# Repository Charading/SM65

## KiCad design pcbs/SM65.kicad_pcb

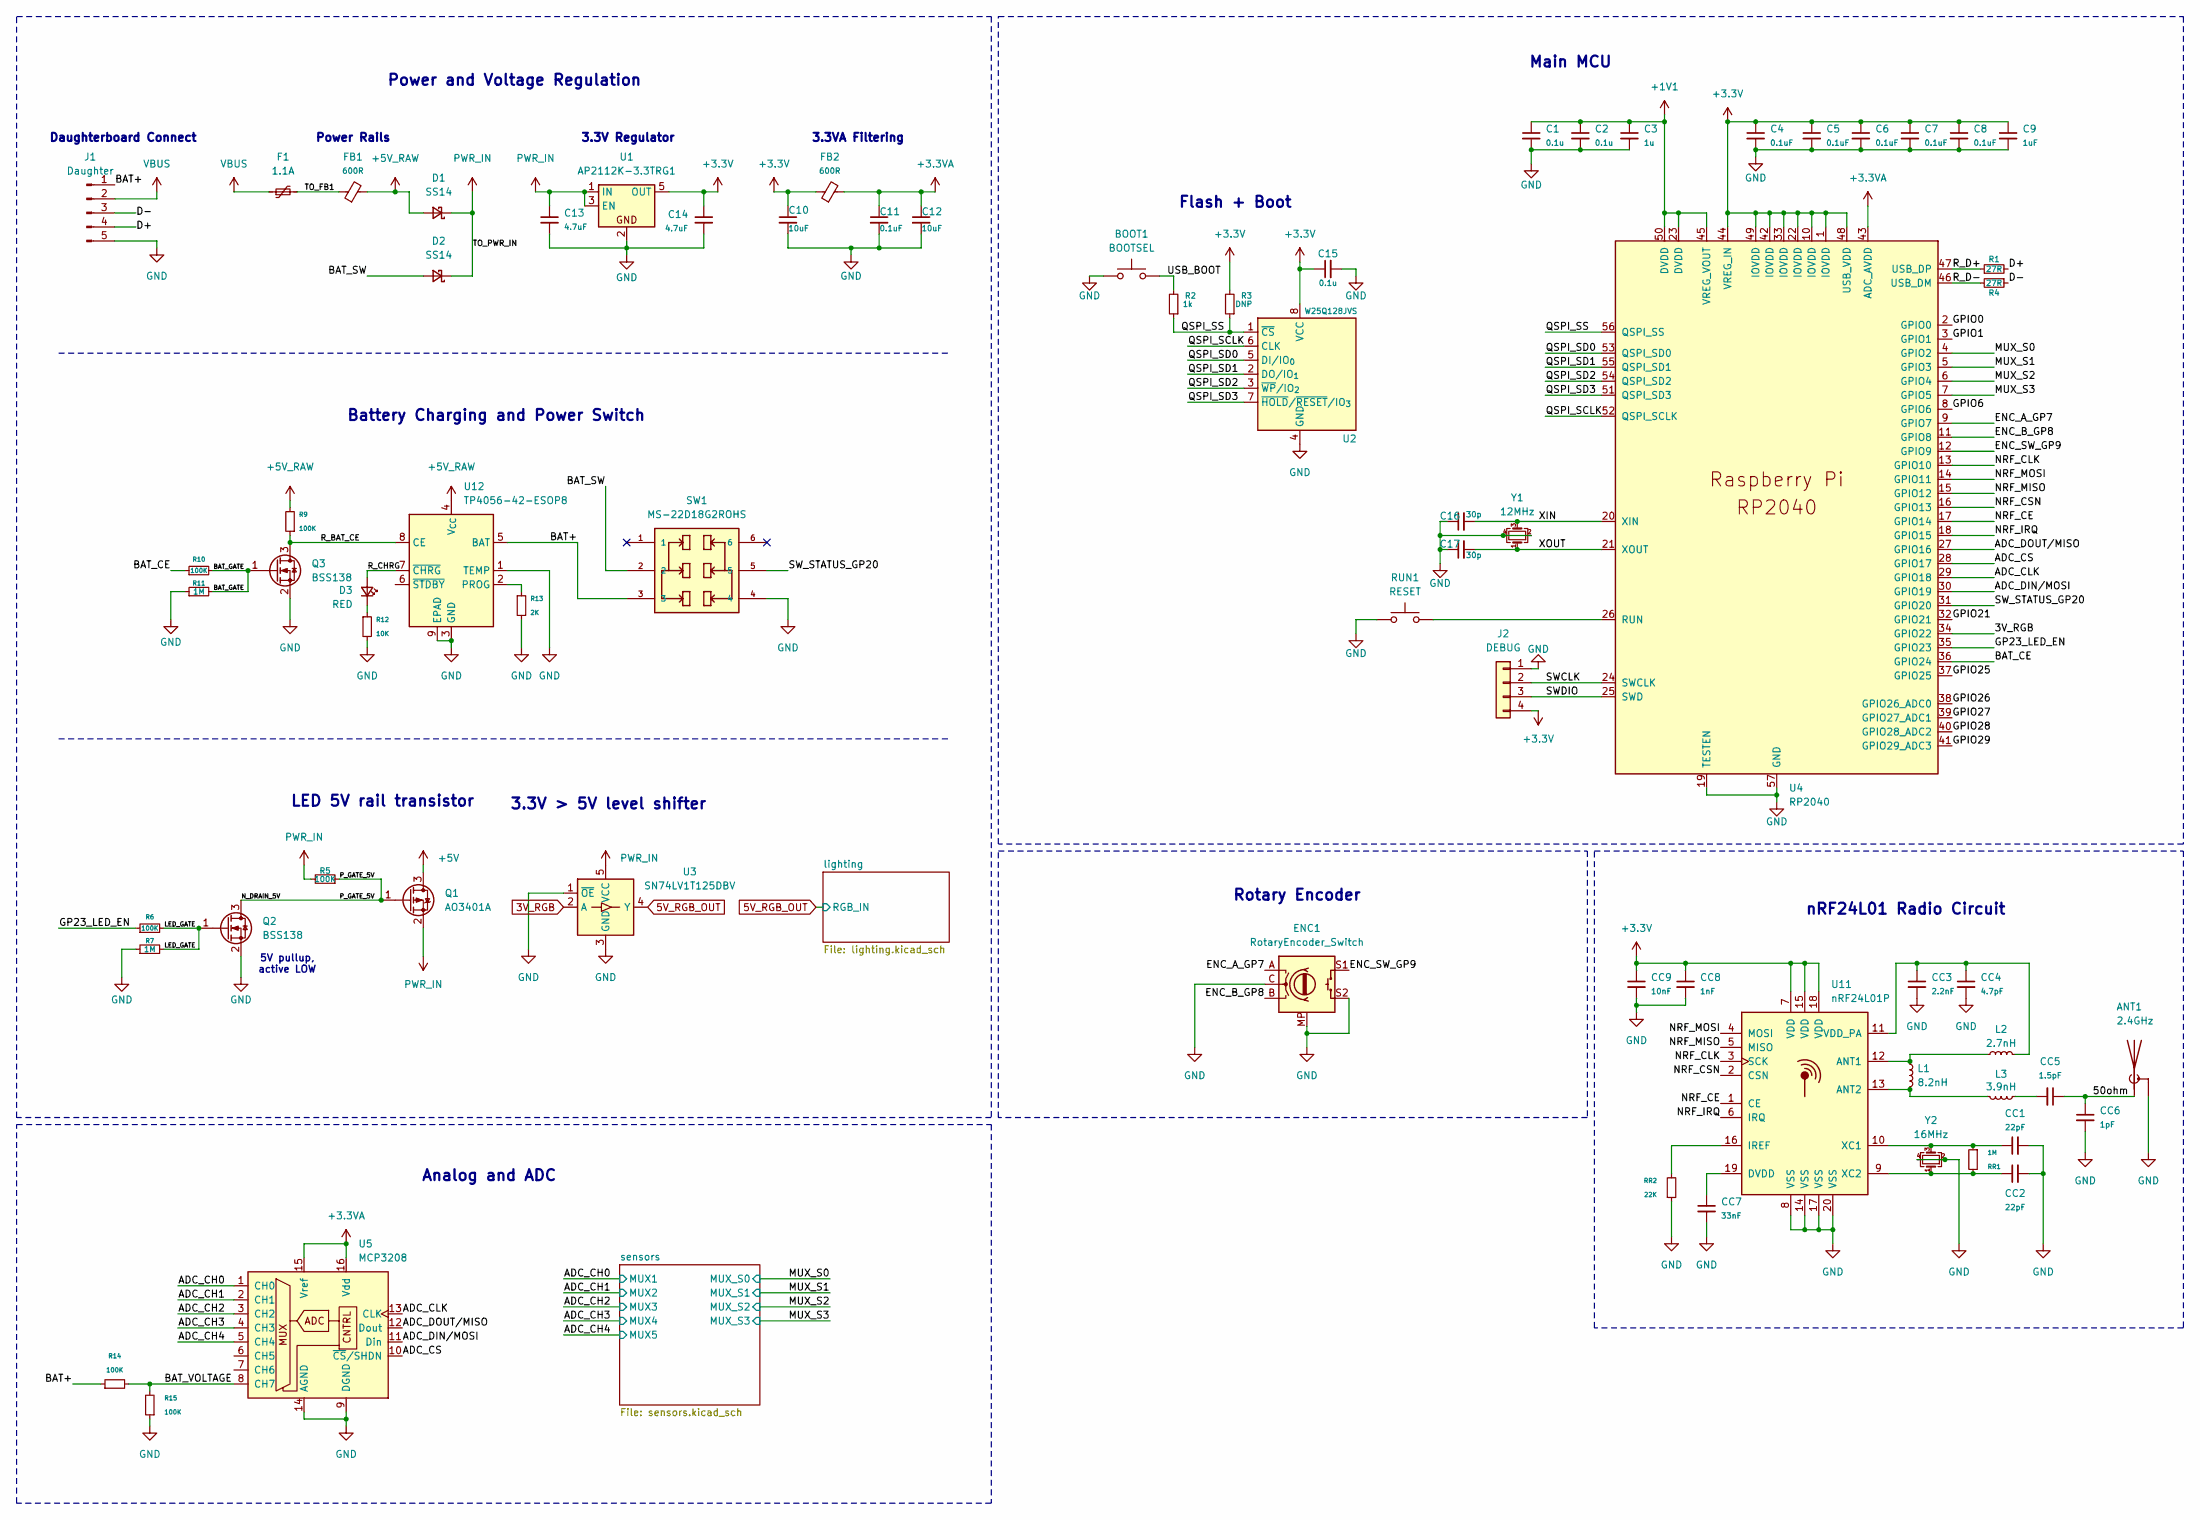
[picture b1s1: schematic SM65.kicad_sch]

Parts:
ANT1: 2.4GHz; MIFA_2.4GHz_Antenna
BOOT1: BOOTSEL; SW_SPST_EVQP2_MiddlePushTravel_H2.5mm
C1, C2: 0.1u; C_0402
C3: 1u; C_0402
C4, C5, C6, C7, C8: 0.1uF; C_0402
C9: 1uF; C_0402
C10, C12: 10uF; C_0603
C11: 0.1uF; C_0603
C13, C14: 4.7uF; C_0603
C15: 0.1u; C_0603
C16, C17: 30p; C_0402
CC1, CC2: 22pF; C_0402
CC3: 2.2nF; C_0402
CC4: 4.7pF; C_0402
CC5: 1.5pF; C_0402
CC6: 1pF; C_0402
CC7: 33nF; C_0402
CC8: 1nF; C_0402
CC9: 10nF; C_0402
D1, D2: SS14; D_SMA
D3: RED; LED_0402_1005Metric
ENC1: RotaryEncoder_Switch; RotaryEncoder_MX_EC11_CircularMountingHoles
F1: 1.1A; Fuse_0603_1608Metric
FB1, FB2: 600R; Ferrite_0603_1608Metric
J1: Daughter; JST_GH_BM05B-GHS-TBT_1x05-1MP_P1.25mm_Vertical
J2: DEBUG; PinHeader_1x04_P1.27mm_Vertical; Part Number 1-0401FBV0T
L1: 8.2nH; R_0402
L2: 2.7nH; R_0402
L3: 3.9nH; R_0402
Q1: AO3401A; SOT-23
Q2, Q3: BSS138; SOT-23
R1, R4: 27R; R_0603_1608Metric_Pad0.98x0.95mm_HandSolder
R2: 1k; R_0603
R3: DNP; R_0603
R5, R6, R9, R10, R14, R15: 100K; R_0603
R7, R11: 1M; R_0603
R12: 10K; R_0402
R13: 2K; R_0603
RR1: 1M; R_0402
RR2: 22K; R_0402
RUN1: RESET; SW_SPST_EVQP2_MiddlePushTravel_H2.5mm
SW1: MS-22D18G2ROHS; MS-22D18_SMD
U1: AP2112K-3.3TRG1; SOT-23-5
U2: W25Q128JVS; SOIC-8_5.3x5.3mm_P1.27mm
U3: SN74LV1T125DBV; SOT-23-5
U4: RP2040; QFN-56-1EP_7x7mm_P0.4mm_EP3.2x3.2mm
U5: MCP3208; SOIC-16_3.9x9.9mm_P1.27mm
U11: nRF24L01P; QFN-20-1EP_4x4mm_P0.5mm_EP2.5x2.5mm
U12: TP4056-42-ESOP8; SOIC-8-1EP_3.9x4.9mm_P1.27mm_EP2.41x3.3mm
Y1: 12MHz; Crystal_SMD_3225-4Pin_3.2x2.5mm
Y2: 16MHz; Crystal_SMD_3225-4Pin_3.2x2.5mm

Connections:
3V_RGB: U3.2 (A), U4.34 (GPIO22)
5V_RGB_OUT: U3.4 (Y); also elsewhere on the board
+1V1: C1.1, C2.1, C3.1, U4.23 (DVDD), U4.45 (VREG_VOUT), U4.50 (DVDD)
+3.3V: C4.1, C5.1, C6.1, C7.1, C8.1, C9.1, C10.1, C14.1, C15.1, CC8.1, CC9.1, FB2.1, J2.4, R3.2, U1.5 (OUT), U2.8 (VCC), U4.1 (IOVDD), U4.10 (IOVDD), U4.22 (IOVDD), U4.33 (IOVDD), U4.42 (IOVDD), U4.44 (VREG_IN), U4.48 (USB_VDD), U4.49 (IOVDD), U11.7 (VDD), U11.15 (VDD), U11.18 (VDD); also elsewhere on the board
+3.3VA: C11.1, C12.1, FB2.2, U4.43 (ADC_AVDD), U5.15 (Vref), U5.16 (Vdd)
+5V: Q1.3 (D); also elsewhere on the board
+5V_RAW: D1.2 (A), FB1.2, R9.2, U12.4 (V_{CC})
/50ohm: ANT1.1 (A), CC5.1, CC6.1
/ADC_CH0: U5.1 (CH0); also elsewhere on the board
/ADC_CH1: U5.2 (CH1); also elsewhere on the board
/ADC_CH2: U5.3 (CH2); also elsewhere on the board
/ADC_CH3: U5.4 (CH3); also elsewhere on the board
/ADC_CH4: U5.5 (CH4); also elsewhere on the board
/ADC_CLK: U4.29 (GPIO18), U5.13 (CLK)
/ADC_CS: U4.28 (GPIO17), U5.10 (~CS/SHDN)
/ADC_DIN/MOSI: U4.30 (GPIO19), U5.11 (Din)
/ADC_DOUT/MISO: U4.27 (GPIO16), U5.12 (Dout)
/BAT+: J1.1, R14.1, SW1.3, U12.5 (BAT)
/BAT_CE: R10.1, U4.36 (GPIO24)
/BAT_GATE: Q3.1 (G), R10.2, R11.2
/BAT_SW: D2.2 (A), SW1.2
/BAT_VOLTAGE: R14.2, R15.2, U5.8 (CH7)
/D+: J1.4, R1.2
/D-: J1.3, R4.1
/ENC_A_GP7: ENC1.A, U4.9 (GPIO7)
/ENC_B_GP8: ENC1.B, U4.11 (GPIO8)
/ENC_SW_GP9: ENC1.S1, U4.12 (GPIO9)
/GP23_LED_EN: R6.1, U4.35 (GPIO23)
/GPIO0: U4.2 (GPIO0)
/GPIO1: U4.3 (GPIO1)
/GPIO6: U4.8 (GPIO6)
/GPIO21: U4.32 (GPIO21)
/GPIO25: U4.37 (GPIO25)
/GPIO26: U4.38 (GPIO26_ADC0)
/GPIO27: U4.39 (GPIO27_ADC1)
/GPIO28: U4.40 (GPIO28_ADC2)
/GPIO29: U4.41 (GPIO29_ADC3)
/LED_GATE: Q2.1 (G), R6.2, R7.2
/MUX_S0: U4.4 (GPIO2); also elsewhere on the board
/MUX_S1: U4.5 (GPIO3); also elsewhere on the board
/MUX_S2: U4.6 (GPIO4); also elsewhere on the board
/MUX_S3: U4.7 (GPIO5); also elsewhere on the board
/NRF_CE: U4.17 (GPIO14), U11.1 (CE)
/NRF_CLK: U4.13 (GPIO10), U11.3 (SCK)
/NRF_CSN: U4.16 (GPIO13), U11.2 (CSN)
/NRF_IRQ: U4.18 (GPIO15), U11.6 (IRQ)
/NRF_MISO: U4.15 (GPIO12), U11.5 (MISO)
/NRF_MOSI: U4.14 (GPIO11), U11.4 (MOSI)
/N_DRAIN_5V: Q1.1 (G), Q2.3 (D), R5.1
/QSPI_SCLK: U2.6 (CLK), U4.52 (QSPI_SCLK)
/QSPI_SD0: U2.5 (DI/IO_{0}), U4.53 (QSPI_SD0)
/QSPI_SD1: U2.2 (DO/IO_{1}), U4.55 (QSPI_SD1)
/QSPI_SD2: U2.3 (~WP/IO_{2}), U4.54 (QSPI_SD2)
/QSPI_SD3: U2.7 (~HOLD/~RESET/IO_{3}), U4.51 (QSPI_SD3)
/QSPI_SS: R2.1, R3.1, U2.1 (~CS), U4.56 (QSPI_SS)
/R_BAT_CE: Q3.3 (D), R9.1, U12.8 (CE)
/R_CHRG: D3.2 (A), U12.7 (~CHRG)
/R_D+: R1.1, U4.47 (USB_DP)
/R_D-: R4.2, U4.46 (USB_DM)
/SWCLK: J2.2, U4.24 (SWCLK)
/SWDIO: J2.3, U4.25 (SWD)
/SW_STATUS_GP20: SW1.5, U4.31 (GPIO20)
/TO_FB1: F1.2, FB1.1
/USB_BOOT: BOOT1.2, R2.2
/XIN: C16.2, U4.20 (XIN), Y1.3
/XOUT: C17.2, U4.21 (XOUT), Y1.1
GND: ANT1.2 (Shield), BOOT1.1, C1.2, C2.2, C3.2, C4.2, C5.2, C6.2, C7.2, C8.2, C9.2, C10.2, C11.2, C12.2, C13.2, C14.2, C15.2, C16.1, C17.1, CC1.2, CC2.2, CC3.2, CC4.2, CC6.2, CC7.2, CC8.2, CC9.2, ENC1.C, ENC1.MP, ENC1.S2, J1.5, J2.1, Q2.2 (S), Q3.2 (S), R7.1, R11.1, R12.2, R13.2, R15.1, RR2.1, RUN1.1, SW1.4, U1.2, U2.4 (GND), U3.1 (~OE), U3.3 (GND), U4.19 (TESTEN), U4.57 (GND), U5.9 (DGND), U5.14 (AGND), U11.8 (VSS), U11.14 (VSS), U11.17 (VSS), U11.20 (VSS), U12.1 (TEMP), U12.3 (GND), U12.9 (EPAD), Y1.2, Y1.4, Y2.2, Y2.4; also elsewhere on the board
unnamed: CC5.2, L3.1
unnamed: D3.1 (K), R12.1
unnamed: RUN1.2, U4.26 (RUN)
unnamed: L1.1, L2.1, U11.12 (ANT1)
unnamed: L1.2, L3.2, U11.13 (ANT2)
unnamed: CC7.1, U11.19 (DVDD)
unnamed: RR2.2, U11.16 (IREF)
unnamed: CC3.1, CC4.1, L2.2, U11.11 (VDD_PA)
unnamed: CC1.1, RR1.1, U11.10 (XC1), Y2.3
unnamed: CC2.1, RR1.2, U11.9 (XC2), Y2.1
unnamed: R13.1, U12.2 (PROG)
PWR_IN: C13.1, D1.1 (K), D2.1 (K), Q1.2 (S), R5.2, U1.1 (IN), U1.3 (EN), U3.5 (VCC)
VBUS: F1.1, J1.2

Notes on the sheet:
LED 5V rail transistor
3.3V > 5V level shifter
Rotary Encoder
Flash + Boot
5V pullup, active LOW
Battery Charging and Power Switch
Daughterboard Connect
Analog and ADC
3.3V Regulator
nRF24L01 Radio Circuit
Power and Voltage Regulation
3.3VA Filtering
Main MCU
Power Rails

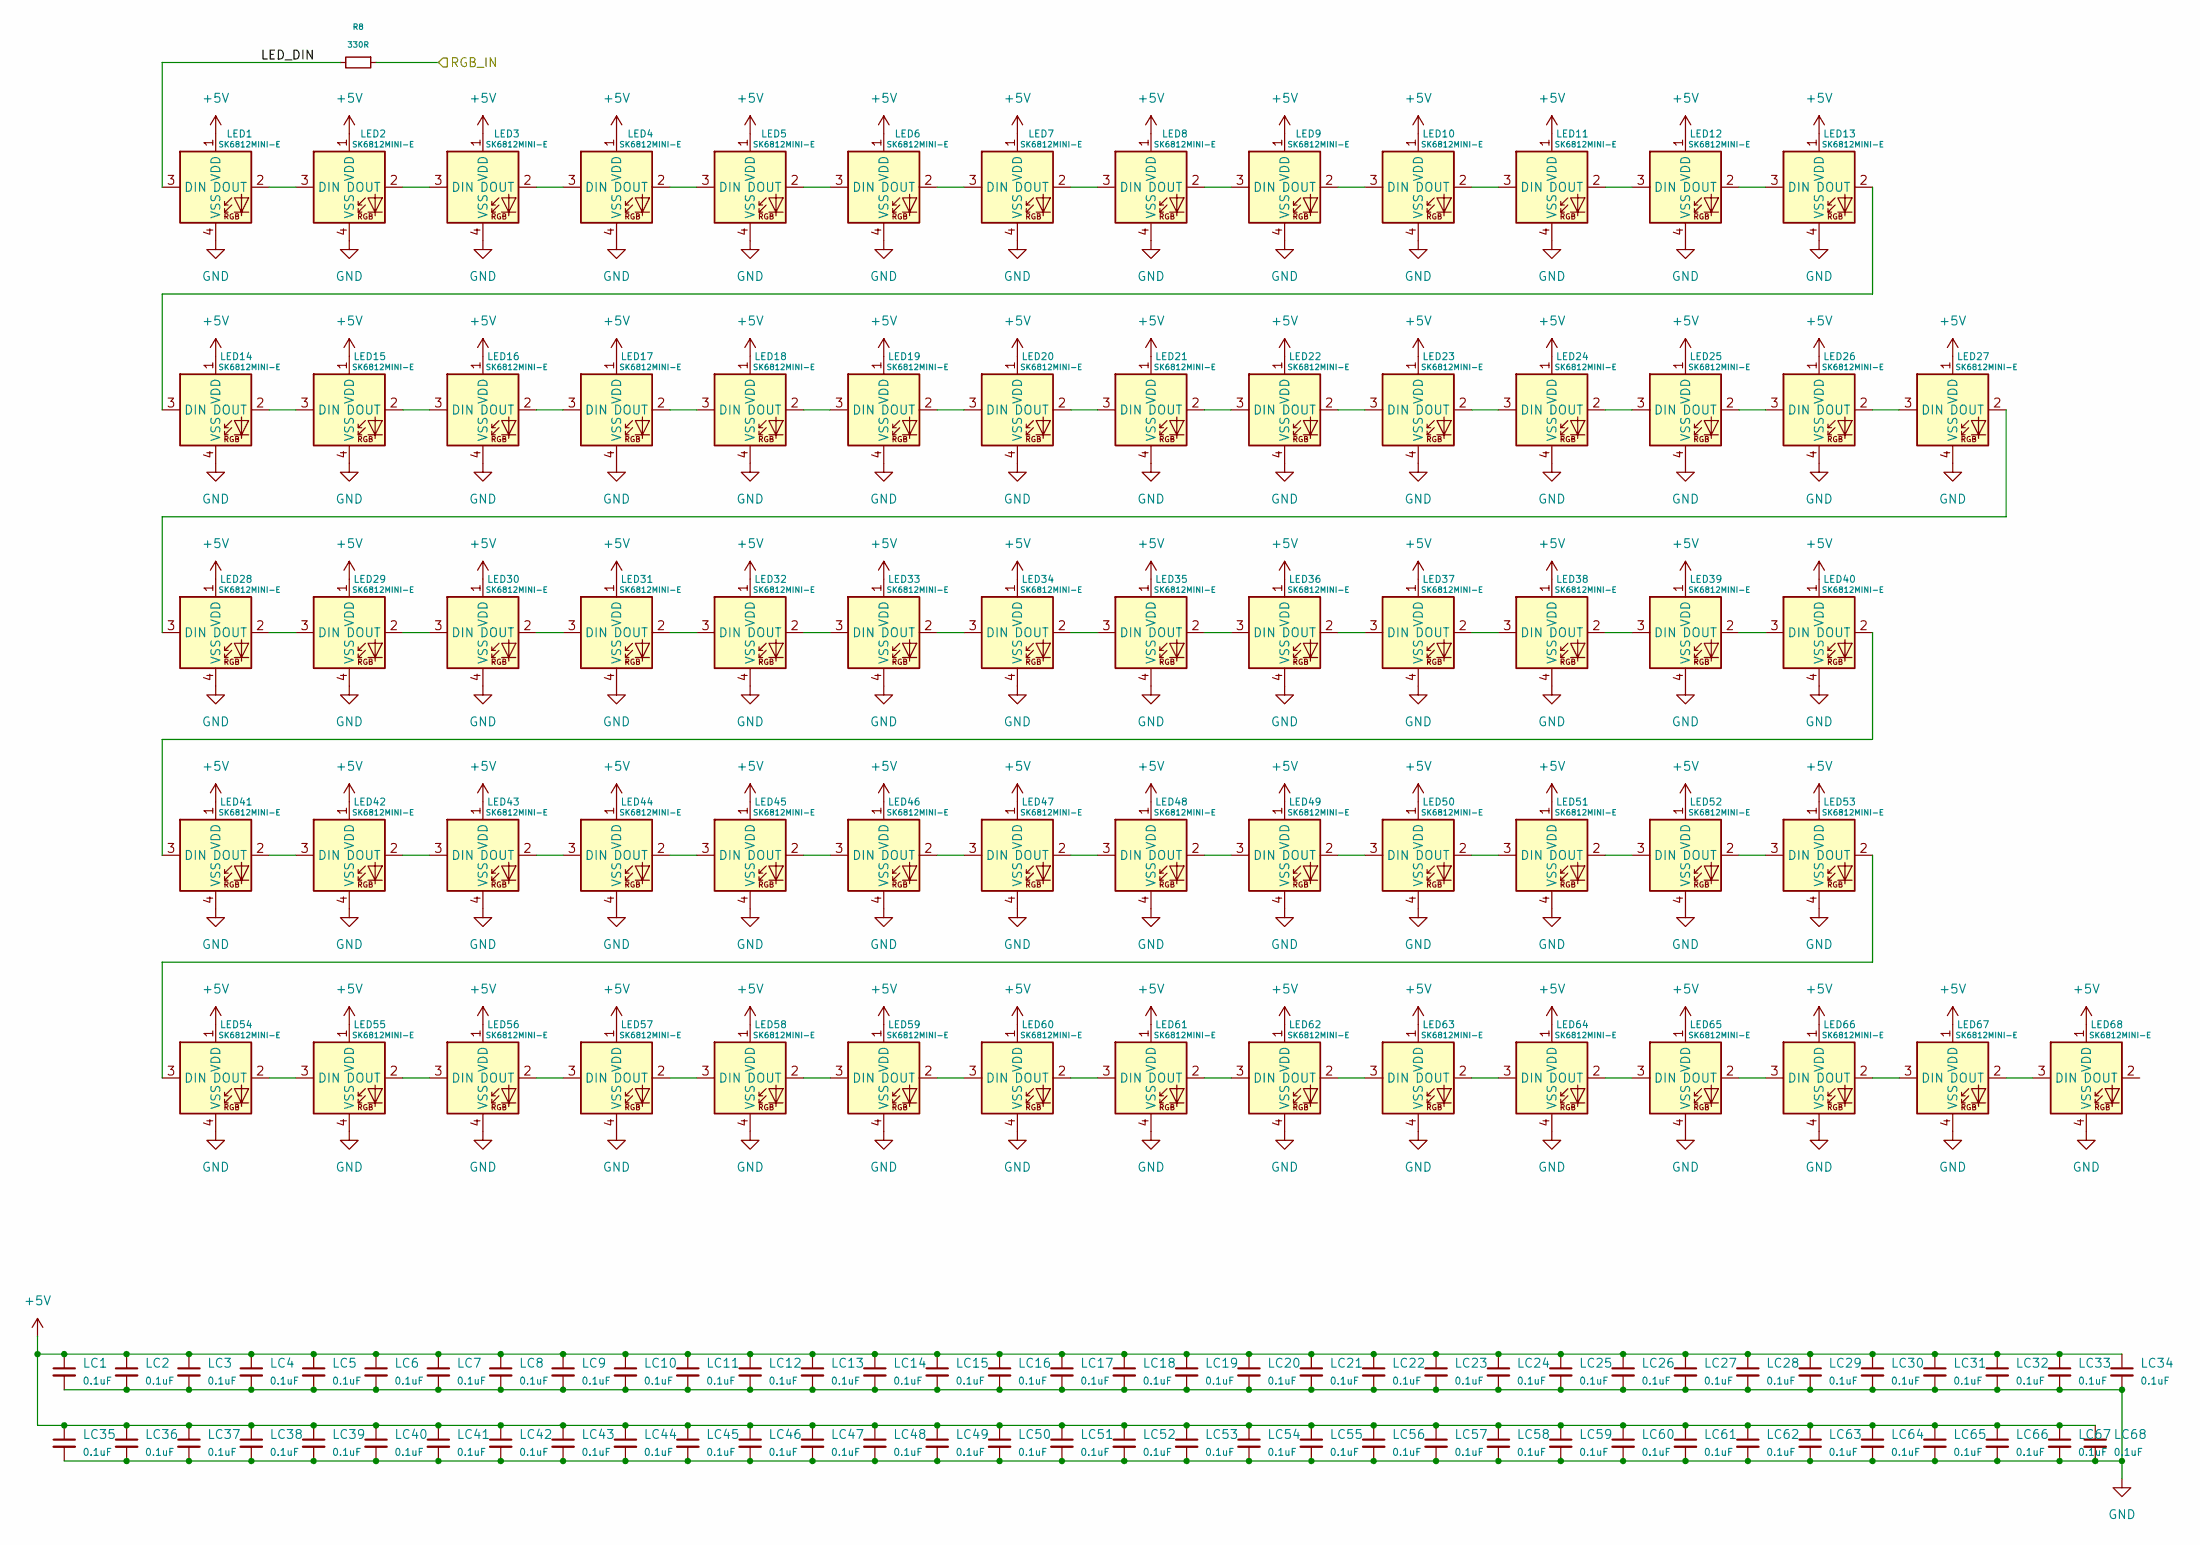
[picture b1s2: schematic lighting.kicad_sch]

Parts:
LC1, LC2, LC3, LC4, LC5, LC6, LC7, LC8, LC9, LC10, LC11, LC12, LC13, LC14, LC15, LC16, LC17, LC18, LC19, LC20, LC21, LC22, LC23, LC24, LC25, LC26, LC27, LC28, LC29, LC30, LC31, LC32, LC33, LC34, LC35, LC36, LC37, LC38, LC39, LC40, LC41, LC42, LC43, LC44, LC45, LC46, LC47, LC48, LC49, LC50, LC51, LC52, LC53, LC54, LC55, LC56, LC57, LC58, LC59, LC60, LC61, LC62, LC63, LC64, LC65, LC66, LC67, LC68: 0.1uF; C_0402
LED1, LED2, LED3, LED4, LED5, LED6, LED7, LED8, LED9, LED10, LED11, LED12, LED13, LED14, LED15, LED16, LED17, LED18, LED19, LED20, LED21, LED22, LED23, LED24, LED25, LED26, LED27, LED28, LED29, LED30, LED31, LED32, LED33, LED34, LED35, LED36, LED37, LED38, LED39, LED40, LED41, LED42, LED43, LED44, LED45, LED46, LED47, LED48, LED49, LED50, LED51, LED52, LED53, LED54, LED55, LED56, LED57, LED58, LED59, LED60, LED61, LED62, LED63, LED64, LED65, LED66, LED67, LED68: SK6812MINI-E; LED_6028R; LCSC C5149201
R8: 330R; R_0603

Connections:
5V_RGB_OUT: R8.1; also elsewhere on the board
+5V: LC1.1, LC2.1, LC3.1, LC4.1, LC5.1, LC6.1, LC7.1, LC8.1, LC9.1, LC10.1, LC11.1, LC12.1, LC13.1, LC14.1, LC15.1, LC16.1, LC17.1, LC18.1, LC19.1, LC20.1, LC21.1, LC22.1, LC23.1, LC24.1, LC25.1, LC26.1, LC27.1, LC28.1, LC29.1, LC30.1, LC31.1, LC32.1, LC33.1, LC34.1, LC35.1, LC36.1, LC37.1, LC38.1, LC39.1, LC40.1, LC41.1, LC42.1, LC43.1, LC44.1, LC45.1, LC46.1, LC47.1, LC48.1, LC49.1, LC50.1, LC51.1, LC52.1, LC53.1, LC54.1, LC55.1, LC56.1, LC57.1, LC58.1, LC59.1, LC60.1, LC61.1, LC62.1, LC63.1, LC64.1, LC65.1, LC66.1, LC67.1, LC68.1, LED1.1 (VDD), LED2.1 (VDD), LED3.1 (VDD), LED4.1 (VDD), LED5.1 (VDD), LED6.1 (VDD), LED7.1 (VDD), LED8.1 (VDD), LED9.1 (VDD), LED10.1 (VDD), LED11.1 (VDD), LED12.1 (VDD), LED13.1 (VDD), LED14.1 (VDD), LED15.1 (VDD), LED16.1 (VDD), LED17.1 (VDD), LED18.1 (VDD), LED19.1 (VDD), LED20.1 (VDD), LED21.1 (VDD), LED22.1 (VDD), LED23.1 (VDD), LED24.1 (VDD), LED25.1 (VDD), LED26.1 (VDD), LED27.1 (VDD), LED28.1 (VDD), LED29.1 (VDD), LED30.1 (VDD), LED31.1 (VDD), LED32.1 (VDD), LED33.1 (VDD), LED34.1 (VDD), LED35.1 (VDD), LED36.1 (VDD), LED37.1 (VDD), LED38.1 (VDD), LED39.1 (VDD), LED40.1 (VDD), LED41.1 (VDD), LED42.1 (VDD), LED43.1 (VDD), LED44.1 (VDD), LED45.1 (VDD), LED46.1 (VDD), LED47.1 (VDD), LED48.1 (VDD), LED49.1 (VDD), LED50.1 (VDD), LED51.1 (VDD), LED52.1 (VDD), LED53.1 (VDD), LED54.1 (VDD), LED55.1 (VDD), LED56.1 (VDD), LED57.1 (VDD), LED58.1 (VDD), LED59.1 (VDD), LED60.1 (VDD), LED61.1 (VDD), LED62.1 (VDD), LED63.1 (VDD), LED64.1 (VDD), LED65.1 (VDD), LED66.1 (VDD), LED67.1 (VDD), LED68.1 (VDD); also elsewhere on the board
/lighting/LED_DIN: LED1.3 (DIN), R8.2
GND: LC1.2, LC2.2, LC3.2, LC4.2, LC5.2, LC6.2, LC7.2, LC8.2, LC9.2, LC10.2, LC11.2, LC12.2, LC13.2, LC14.2, LC15.2, LC16.2, LC17.2, LC18.2, LC19.2, LC20.2, LC21.2, LC22.2, LC23.2, LC24.2, LC25.2, LC26.2, LC27.2, LC28.2, LC29.2, LC30.2, LC31.2, LC32.2, LC33.2, LC34.2, LC35.2, LC36.2, LC37.2, LC38.2, LC39.2, LC40.2, LC41.2, LC42.2, LC43.2, LC44.2, LC45.2, LC46.2, LC47.2, LC48.2, LC49.2, LC50.2, LC51.2, LC52.2, LC53.2, LC54.2, LC55.2, LC56.2, LC57.2, LC58.2, LC59.2, LC60.2, LC61.2, LC62.2, LC63.2, LC64.2, LC65.2, LC66.2, LC67.2, LC68.2, LED1.4 (VSS), LED2.4 (VSS), LED3.4 (VSS), LED4.4 (VSS), LED5.4 (VSS), LED6.4 (VSS), LED7.4 (VSS), LED8.4 (VSS), LED9.4 (VSS), LED10.4 (VSS), LED11.4 (VSS), LED12.4 (VSS), LED13.4 (VSS), LED14.4 (VSS), LED15.4 (VSS), LED16.4 (VSS), LED17.4 (VSS), LED18.4 (VSS), LED19.4 (VSS), LED20.4 (VSS), LED21.4 (VSS), LED22.4 (VSS), LED23.4 (VSS), LED24.4 (VSS), LED25.4 (VSS), LED26.4 (VSS), LED27.4 (VSS), LED28.4 (VSS), LED29.4 (VSS), LED30.4 (VSS), LED31.4 (VSS), LED32.4 (VSS), LED33.4 (VSS), LED34.4 (VSS), LED35.4 (VSS), LED36.4 (VSS), LED37.4 (VSS), LED38.4 (VSS), LED39.4 (VSS), LED40.4 (VSS), LED41.4 (VSS), LED42.4 (VSS), LED43.4 (VSS), LED44.4 (VSS), LED45.4 (VSS), LED46.4 (VSS), LED47.4 (VSS), LED48.4 (VSS), LED49.4 (VSS), LED50.4 (VSS), LED51.4 (VSS), LED52.4 (VSS), LED53.4 (VSS), LED54.4 (VSS), LED55.4 (VSS), LED56.4 (VSS), LED57.4 (VSS), LED58.4 (VSS), LED59.4 (VSS), LED60.4 (VSS), LED61.4 (VSS), LED62.4 (VSS), LED63.4 (VSS), LED64.4 (VSS), LED65.4 (VSS), LED66.4 (VSS), LED67.4 (VSS), LED68.4 (VSS); also elsewhere on the board
unnamed: LED1.2 (DOUT), LED2.3 (DIN)
unnamed: LED2.2 (DOUT), LED3.3 (DIN)
unnamed: LED3.2 (DOUT), LED4.3 (DIN)
unnamed: LED4.2 (DOUT), LED5.3 (DIN)
unnamed: LED5.2 (DOUT), LED6.3 (DIN)
unnamed: LED6.2 (DOUT), LED7.3 (DIN)
unnamed: LED7.2 (DOUT), LED8.3 (DIN)
unnamed: LED8.2 (DOUT), LED9.3 (DIN)
unnamed: LED9.2 (DOUT), LED10.3 (DIN)
unnamed: LED10.2 (DOUT), LED11.3 (DIN)
unnamed: LED11.2 (DOUT), LED12.3 (DIN)
unnamed: LED12.2 (DOUT), LED13.3 (DIN)
unnamed: LED13.2 (DOUT), LED14.3 (DIN)
unnamed: LED14.2 (DOUT), LED15.3 (DIN)
unnamed: LED15.2 (DOUT), LED16.3 (DIN)
unnamed: LED16.2 (DOUT), LED17.3 (DIN)
unnamed: LED17.2 (DOUT), LED18.3 (DIN)
unnamed: LED18.2 (DOUT), LED19.3 (DIN)
unnamed: LED19.2 (DOUT), LED20.3 (DIN)
unnamed: LED20.2 (DOUT), LED21.3 (DIN)
unnamed: LED21.2 (DOUT), LED22.3 (DIN)
unnamed: LED22.2 (DOUT), LED23.3 (DIN)
unnamed: LED23.2 (DOUT), LED24.3 (DIN)
unnamed: LED24.2 (DOUT), LED25.3 (DIN)
unnamed: LED25.2 (DOUT), LED26.3 (DIN)
unnamed: LED26.2 (DOUT), LED27.3 (DIN)
unnamed: LED27.2 (DOUT), LED28.3 (DIN)
unnamed: LED28.2 (DOUT), LED29.3 (DIN)
unnamed: LED29.2 (DOUT), LED30.3 (DIN)
unnamed: LED30.2 (DOUT), LED31.3 (DIN)
unnamed: LED31.2 (DOUT), LED32.3 (DIN)
unnamed: LED32.2 (DOUT), LED33.3 (DIN)
unnamed: LED33.2 (DOUT), LED34.3 (DIN)
unnamed: LED34.2 (DOUT), LED35.3 (DIN)
unnamed: LED35.2 (DOUT), LED36.3 (DIN)
unnamed: LED36.2 (DOUT), LED37.3 (DIN)
unnamed: LED37.2 (DOUT), LED38.3 (DIN)
unnamed: LED38.2 (DOUT), LED39.3 (DIN)
unnamed: LED39.2 (DOUT), LED40.3 (DIN)
unnamed: LED40.2 (DOUT), LED41.3 (DIN)
unnamed: LED41.2 (DOUT), LED42.3 (DIN)
unnamed: LED42.2 (DOUT), LED43.3 (DIN)
unnamed: LED43.2 (DOUT), LED44.3 (DIN)
unnamed: LED44.2 (DOUT), LED45.3 (DIN)
unnamed: LED45.2 (DOUT), LED46.3 (DIN)
unnamed: LED46.2 (DOUT), LED47.3 (DIN)
unnamed: LED47.2 (DOUT), LED48.3 (DIN)
unnamed: LED48.2 (DOUT), LED49.3 (DIN)
unnamed: LED49.2 (DOUT), LED50.3 (DIN)
unnamed: LED50.2 (DOUT), LED51.3 (DIN)
unnamed: LED51.2 (DOUT), LED52.3 (DIN)
unnamed: LED52.2 (DOUT), LED53.3 (DIN)
unnamed: LED53.2 (DOUT), LED54.3 (DIN)
unnamed: LED54.2 (DOUT), LED55.3 (DIN)
unnamed: LED55.2 (DOUT), LED56.3 (DIN)
unnamed: LED56.2 (DOUT), LED57.3 (DIN)
unnamed: LED57.2 (DOUT), LED58.3 (DIN)
unnamed: LED58.2 (DOUT), LED59.3 (DIN)
unnamed: LED59.2 (DOUT), LED60.3 (DIN)
unnamed: LED60.2 (DOUT), LED61.3 (DIN)
unnamed: LED61.2 (DOUT), LED62.3 (DIN)
unnamed: LED62.2 (DOUT), LED63.3 (DIN)
unnamed: LED63.2 (DOUT), LED64.3 (DIN)
unnamed: LED64.2 (DOUT), LED65.3 (DIN)
unnamed: LED65.2 (DOUT), LED66.3 (DIN)
unnamed: LED66.2 (DOUT), LED67.3 (DIN)
unnamed: LED67.2 (DOUT), LED68.3 (DIN)

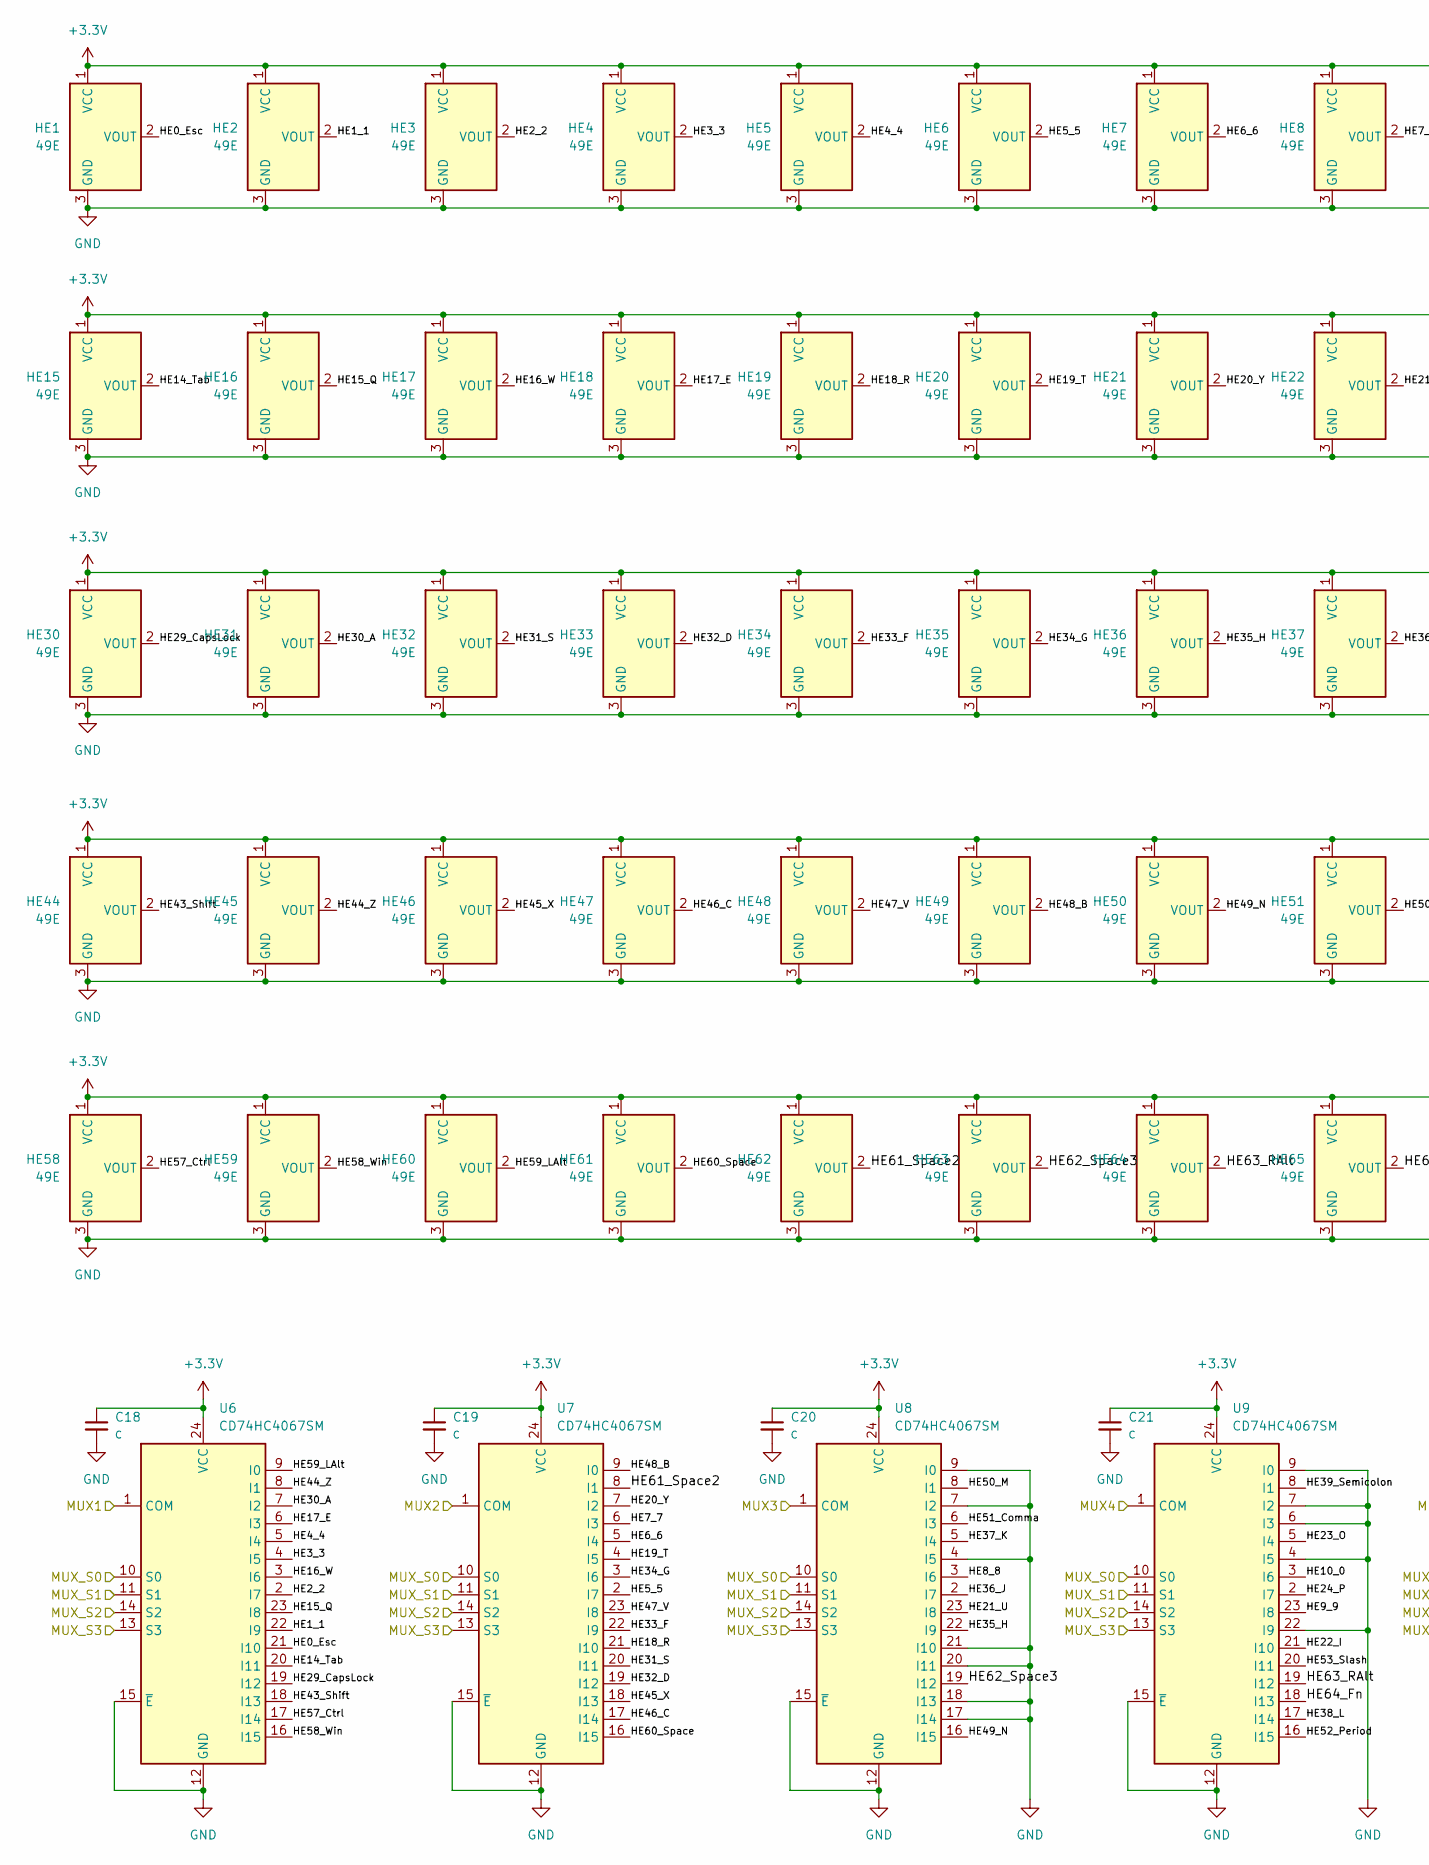
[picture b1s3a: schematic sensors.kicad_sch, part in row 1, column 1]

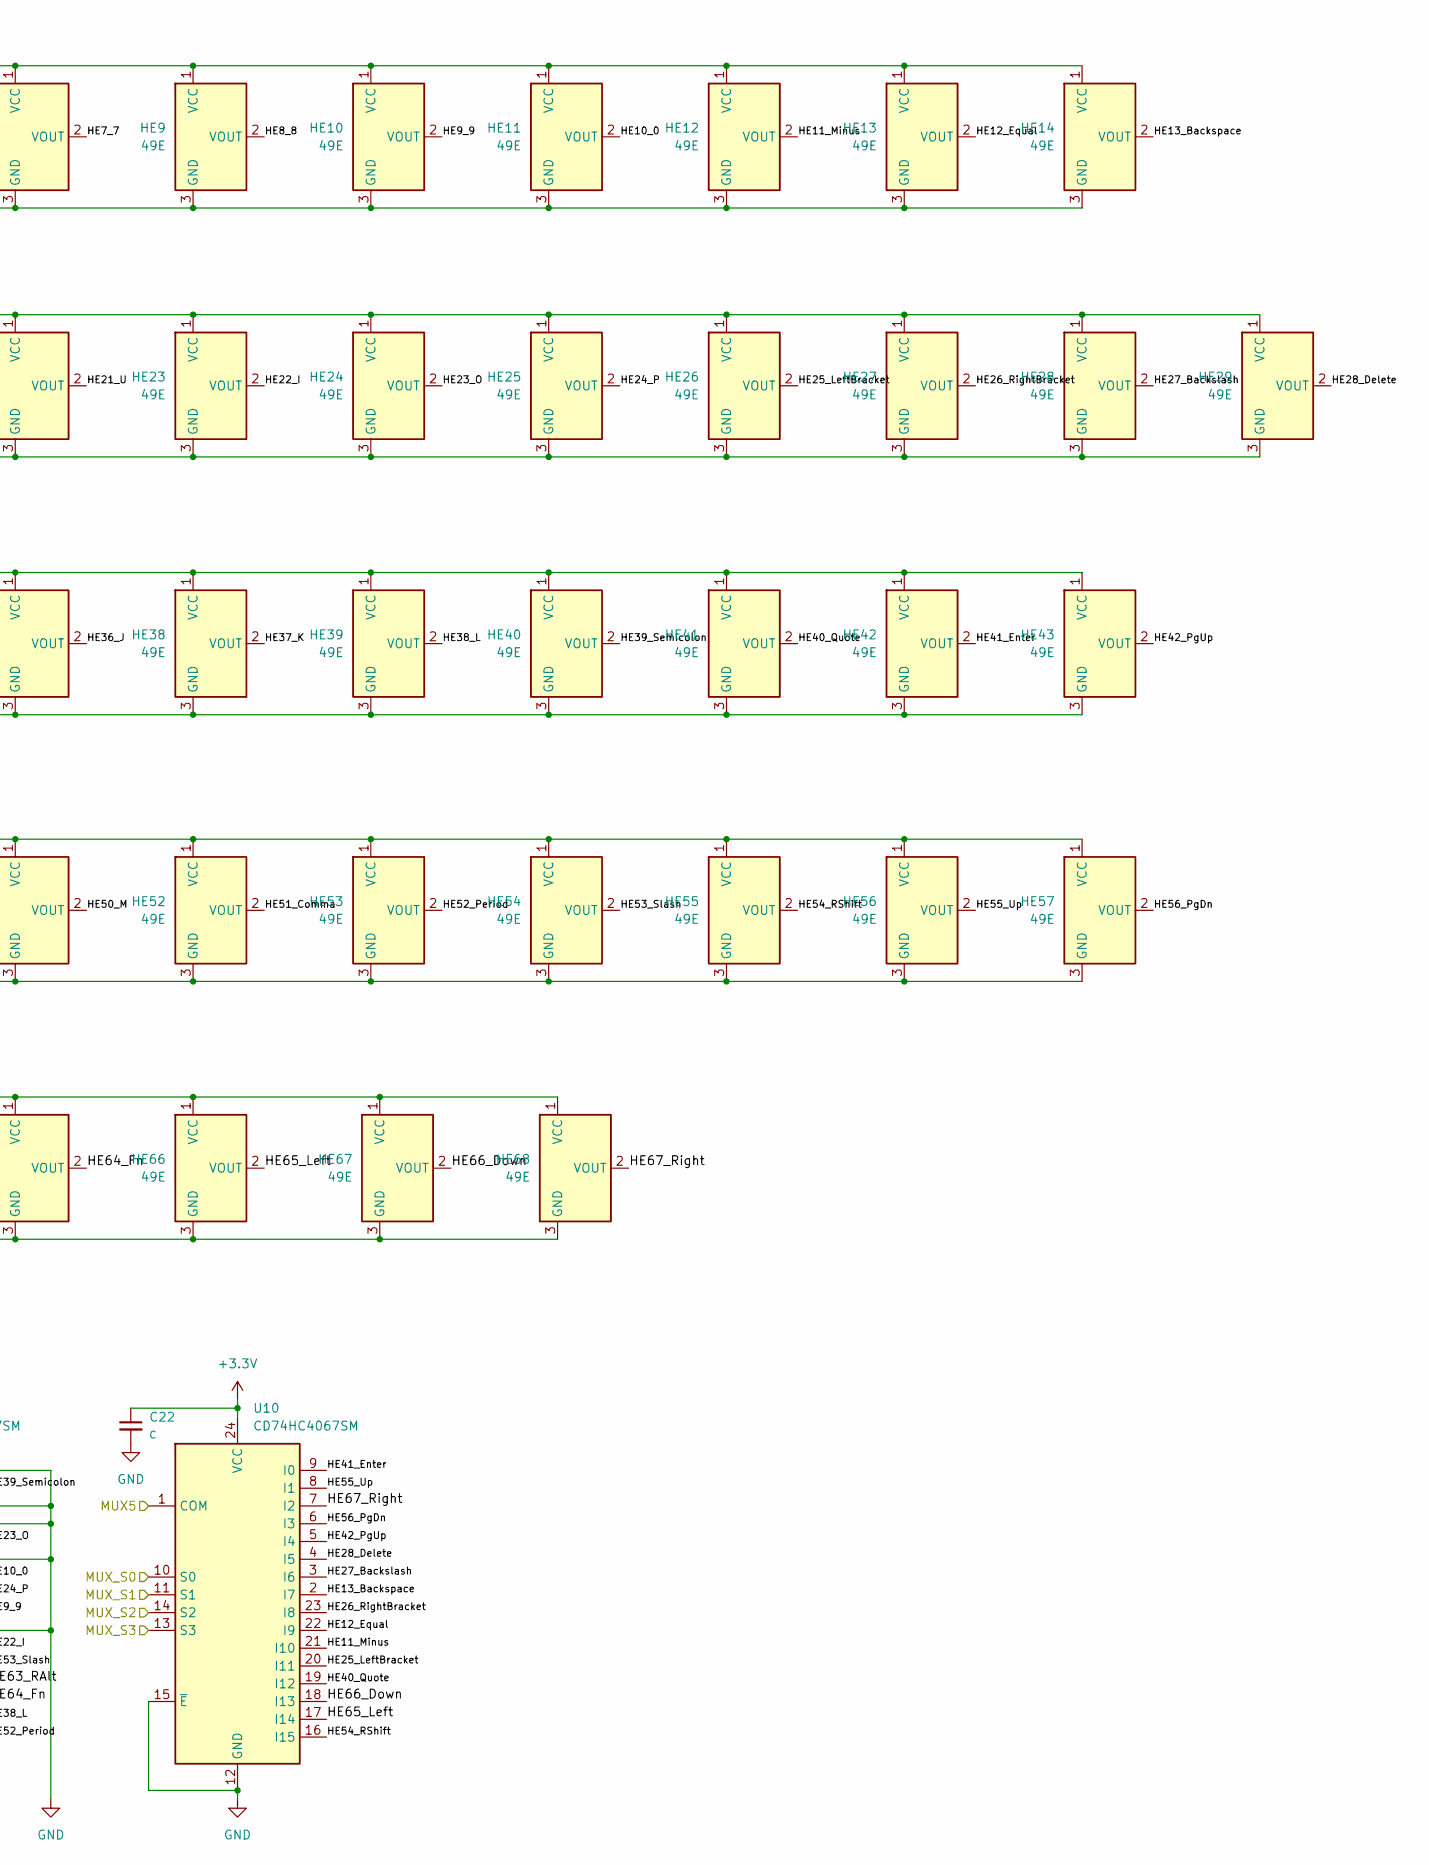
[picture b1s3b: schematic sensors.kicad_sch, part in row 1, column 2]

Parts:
C18, C19, C20, C21, C22: C; C_0402
HE1, HE2, HE3, HE4, HE5, HE6, HE7, HE8, HE9, HE10, HE11, HE12, HE13, HE16, HE17, HE18, HE19, HE20, HE21, HE22, HE23, HE24, HE25, HE26, HE27, HE29, HE31, HE32, HE33, HE34, HE35, HE36, HE37, HE38, HE39, HE40, HE41, HE43, HE45, HE46, HE47, HE48, HE49, HE50, HE51, HE52, HE53, HE54, HE55, HE56, HE57, HE66, HE67, HE68: 49E; SW_MX_HE_90deg_1u_Rules; LCSC C7420984
HE14: 49E; SW_MX_HE_90deg_2.00u_Rules; LCSC C7420984
HE15, HE28: 49E; SW_MX_HE_90deg_1.5u_Rules; LCSC C7420984
HE30: 49E; SW_MX_HE_90deg_1.75u_Rules; LCSC C7420984
HE42, HE44, HE61: 49E; SW_MX_HE_90deg_2.25u_Rules; LCSC C7420984
HE58, HE59, HE60, HE62, HE64, HE65: 49E; SW_MX_HE_90deg_1.25u_Rules; LCSC C7420984
HE63: 49E; SW_MX_HE_90deg_2.75u_Rules; LCSC C7420984
U6, U7, U8, U9, U10: CD74HC4067SM; SSOP-24_5.3x8.2mm_P0.65mm

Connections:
+3.3V: C18.1, C19.1, C20.1, C21.1, C22.1, HE1.1 (VCC), HE2.1 (VCC), HE3.1 (VCC), HE4.1 (VCC), HE5.1 (VCC), HE6.1 (VCC), HE7.1 (VCC), HE8.1 (VCC), HE9.1 (VCC), HE10.1 (VCC), HE11.1 (VCC), HE12.1 (VCC), HE13.1 (VCC), HE14.1 (VCC), HE15.1 (VCC), HE16.1 (VCC), HE17.1 (VCC), HE18.1 (VCC), HE19.1 (VCC), HE20.1 (VCC), HE21.1 (VCC), HE22.1 (VCC), HE23.1 (VCC), HE24.1 (VCC), HE25.1 (VCC), HE26.1 (VCC), HE27.1 (VCC), HE28.1 (VCC), HE29.1 (VCC), HE30.1 (VCC), HE31.1 (VCC), HE32.1 (VCC), HE33.1 (VCC), HE34.1 (VCC), HE35.1 (VCC), HE36.1 (VCC), HE37.1 (VCC), HE38.1 (VCC), HE39.1 (VCC), HE40.1 (VCC), HE41.1 (VCC), HE42.1 (VCC), HE43.1 (VCC), HE44.1 (VCC), HE45.1 (VCC), HE46.1 (VCC), HE47.1 (VCC), HE48.1 (VCC), HE49.1 (VCC), HE50.1 (VCC), HE51.1 (VCC), HE52.1 (VCC), HE53.1 (VCC), HE54.1 (VCC), HE55.1 (VCC), HE56.1 (VCC), HE57.1 (VCC), HE58.1 (VCC), HE59.1 (VCC), HE60.1 (VCC), HE61.1 (VCC), HE62.1 (VCC), HE63.1 (VCC), HE64.1 (VCC), HE65.1 (VCC), HE66.1 (VCC), HE67.1 (VCC), HE68.1 (VCC), U6.24 (VCC), U7.24 (VCC), U8.24 (VCC), U9.24 (VCC), U10.24 (VCC); also elsewhere on the board
/ADC_CH0: U6.1 (COM); also elsewhere on the board
/ADC_CH1: U7.1 (COM); also elsewhere on the board
/ADC_CH2: U8.1 (COM); also elsewhere on the board
/ADC_CH3: U9.1 (COM); also elsewhere on the board
/ADC_CH4: U10.1 (COM); also elsewhere on the board
/MUX_S0: U6.10 (S0), U7.10 (S0), U8.10 (S0), U9.10 (S0), U10.10 (S0); also elsewhere on the board
/MUX_S1: U6.11 (S1), U7.11 (S1), U8.11 (S1), U9.11 (S1), U10.11 (S1); also elsewhere on the board
/MUX_S2: U6.14 (S2), U7.14 (S2), U8.14 (S2), U9.14 (S2), U10.14 (S2); also elsewhere on the board
/MUX_S3: U6.13 (S3), U7.13 (S3), U8.13 (S3), U9.13 (S3), U10.13 (S3); also elsewhere on the board
/sensors/HE0_Esc: HE1.2 (VOUT), U6.21 (I10)
/sensors/HE1_1: HE2.2 (VOUT), U6.22 (I9)
/sensors/HE2_2: HE3.2 (VOUT), U6.2 (I7)
/sensors/HE3_3: HE4.2 (VOUT), U6.4 (I5)
/sensors/HE4_4: HE5.2 (VOUT), U6.5 (I4)
/sensors/HE5_5: HE6.2 (VOUT), U7.2 (I7)
/sensors/HE6_6: HE7.2 (VOUT), U7.5 (I4)
/sensors/HE7_7: HE8.2 (VOUT), U7.6 (I3)
/sensors/HE8_8: HE9.2 (VOUT), U8.3 (I6)
/sensors/HE9_9: HE10.2 (VOUT), U9.23 (I8)
/sensors/HE10_0: HE11.2 (VOUT), U9.3 (I6)
/sensors/HE11_Minus: HE12.2 (VOUT), U10.21 (I10)
/sensors/HE12_Equal: HE13.2 (VOUT), U10.22 (I9)
/sensors/HE13_Backspace: HE14.2 (VOUT), U10.2 (I7)
/sensors/HE14_Tab: HE15.2 (VOUT), U6.20 (I11)
/sensors/HE15_Q: HE16.2 (VOUT), U6.23 (I8)
/sensors/HE16_W: HE17.2 (VOUT), U6.3 (I6)
/sensors/HE17_E: HE18.2 (VOUT), U6.6 (I3)
/sensors/HE18_R: HE19.2 (VOUT), U7.21 (I10)
/sensors/HE19_T: HE20.2 (VOUT), U7.4 (I5)
/sensors/HE20_Y: HE21.2 (VOUT), U7.7 (I2)
/sensors/HE21_U: HE22.2 (VOUT), U8.23 (I8)
/sensors/HE22_I: HE23.2 (VOUT), U9.21 (I10)
/sensors/HE23_O: HE24.2 (VOUT), U9.5 (I4)
/sensors/HE24_P: HE25.2 (VOUT), U9.2 (I7)
/sensors/HE25_LeftBracket: HE26.2 (VOUT), U10.20 (I11)
/sensors/HE26_RightBracket: HE27.2 (VOUT), U10.23 (I8)
/sensors/HE27_Backslash: HE28.2 (VOUT), U10.3 (I6)
/sensors/HE28_Delete: HE29.2 (VOUT), U10.4 (I5)
/sensors/HE29_CapsLock: HE30.2 (VOUT), U6.19 (I12)
/sensors/HE30_A: HE31.2 (VOUT), U6.7 (I2)
/sensors/HE31_S: HE32.2 (VOUT), U7.20 (I11)
/sensors/HE32_D: HE33.2 (VOUT), U7.19 (I12)
/sensors/HE33_F: HE34.2 (VOUT), U7.22 (I9)
/sensors/HE34_G: HE35.2 (VOUT), U7.3 (I6)
/sensors/HE35_H: HE36.2 (VOUT), U8.22 (I9)
/sensors/HE36_J: HE37.2 (VOUT), U8.2 (I7)
/sensors/HE37_K: HE38.2 (VOUT), U8.5 (I4)
/sensors/HE38_L: HE39.2 (VOUT), U9.17 (I14)
/sensors/HE39_Semicolon: HE40.2 (VOUT), U9.8 (I1)
/sensors/HE40_Quote: HE41.2 (VOUT), U10.19 (I12)
/sensors/HE41_Enter: HE42.2 (VOUT), U10.9 (I0)
/sensors/HE42_PgUp: HE43.2 (VOUT), U10.5 (I4)
/sensors/HE43_Shift: HE44.2 (VOUT), U6.18 (I13)
/sensors/HE44_Z: HE45.2 (VOUT), U6.8 (I1)
/sensors/HE45_X: HE46.2 (VOUT), U7.18 (I13)
/sensors/HE46_C: HE47.2 (VOUT), U7.17 (I14)
/sensors/HE47_V: HE48.2 (VOUT), U7.23 (I8)
/sensors/HE48_B: HE49.2 (VOUT), U7.9 (I0)
/sensors/HE49_N: HE50.2 (VOUT), U8.16 (I15)
/sensors/HE50_M: HE51.2 (VOUT), U8.8 (I1)
/sensors/HE51_Comma: HE52.2 (VOUT), U8.6 (I3)
/sensors/HE52_Period: HE53.2 (VOUT), U9.16 (I15)
/sensors/HE53_Slash: HE54.2 (VOUT), U9.20 (I11)
/sensors/HE54_RShift: HE55.2 (VOUT), U10.16 (I15)
/sensors/HE55_Up: HE56.2 (VOUT), U10.8 (I1)
/sensors/HE56_PgDn: HE57.2 (VOUT), U10.6 (I3)
/sensors/HE57_Ctrl: HE58.2 (VOUT), U6.17 (I14)
/sensors/HE58_Win: HE59.2 (VOUT), U6.16 (I15)
/sensors/HE59_LAlt: HE60.2 (VOUT), U6.9 (I0)
/sensors/HE60_Space: HE61.2 (VOUT), U7.16 (I15)
/sensors/HE61_Space2: HE62.2 (VOUT), U7.8 (I1)
/sensors/HE62_Space3: HE63.2 (VOUT), U8.19 (I12)
/sensors/HE63_RAlt: HE64.2 (VOUT), U9.19 (I12)
/sensors/HE64_Fn: HE65.2 (VOUT), U9.18 (I13)
/sensors/HE65_Left: HE66.2 (VOUT), U10.17 (I14)
/sensors/HE66_Down: HE67.2 (VOUT), U10.18 (I13)
/sensors/HE67_Right: HE68.2 (VOUT), U10.7 (I2)
GND: C18.2, C19.2, C20.2, C21.2, C22.2, HE1.3 (GND), HE2.3 (GND), HE3.3 (GND), HE4.3 (GND), HE5.3 (GND), HE6.3 (GND), HE7.3 (GND), HE8.3 (GND), HE9.3 (GND), HE10.3 (GND), HE11.3 (GND), HE12.3 (GND), HE13.3 (GND), HE14.3 (GND), HE15.3 (GND), HE16.3 (GND), HE17.3 (GND), HE18.3 (GND), HE19.3 (GND), HE20.3 (GND), HE21.3 (GND), HE22.3 (GND), HE23.3 (GND), HE24.3 (GND), HE25.3 (GND), HE26.3 (GND), HE27.3 (GND), HE28.3 (GND), HE29.3 (GND), HE30.3 (GND), HE31.3 (GND), HE32.3 (GND), HE33.3 (GND), HE34.3 (GND), HE35.3 (GND), HE36.3 (GND), HE37.3 (GND), HE38.3 (GND), HE39.3 (GND), HE40.3 (GND), HE41.3 (GND), HE42.3 (GND), HE43.3 (GND), HE44.3 (GND), HE45.3 (GND), HE46.3 (GND), HE47.3 (GND), HE48.3 (GND), HE49.3 (GND), HE50.3 (GND), HE51.3 (GND), HE52.3 (GND), HE53.3 (GND), HE54.3 (GND), HE55.3 (GND), HE56.3 (GND), HE57.3 (GND), HE58.3 (GND), HE59.3 (GND), HE60.3 (GND), HE61.3 (GND), HE62.3 (GND), HE63.3 (GND), HE64.3 (GND), HE65.3 (GND), HE66.3 (GND), HE67.3 (GND), HE68.3 (GND), U6.12 (GND), U6.15 (~E), U7.12 (GND), U7.15 (~E), U8.4 (I5), U8.7 (I2), U8.9 (I0), U8.12 (GND), U8.15 (~E), U8.17 (I14), U8.18 (I13), U8.20 (I11), U8.21 (I10), U9.4 (I5), U9.6 (I3), U9.7 (I2), U9.9 (I0), U9.12 (GND), U9.15 (~E), U9.22 (I9), U10.12 (GND), U10.15 (~E); also elsewhere on the board
